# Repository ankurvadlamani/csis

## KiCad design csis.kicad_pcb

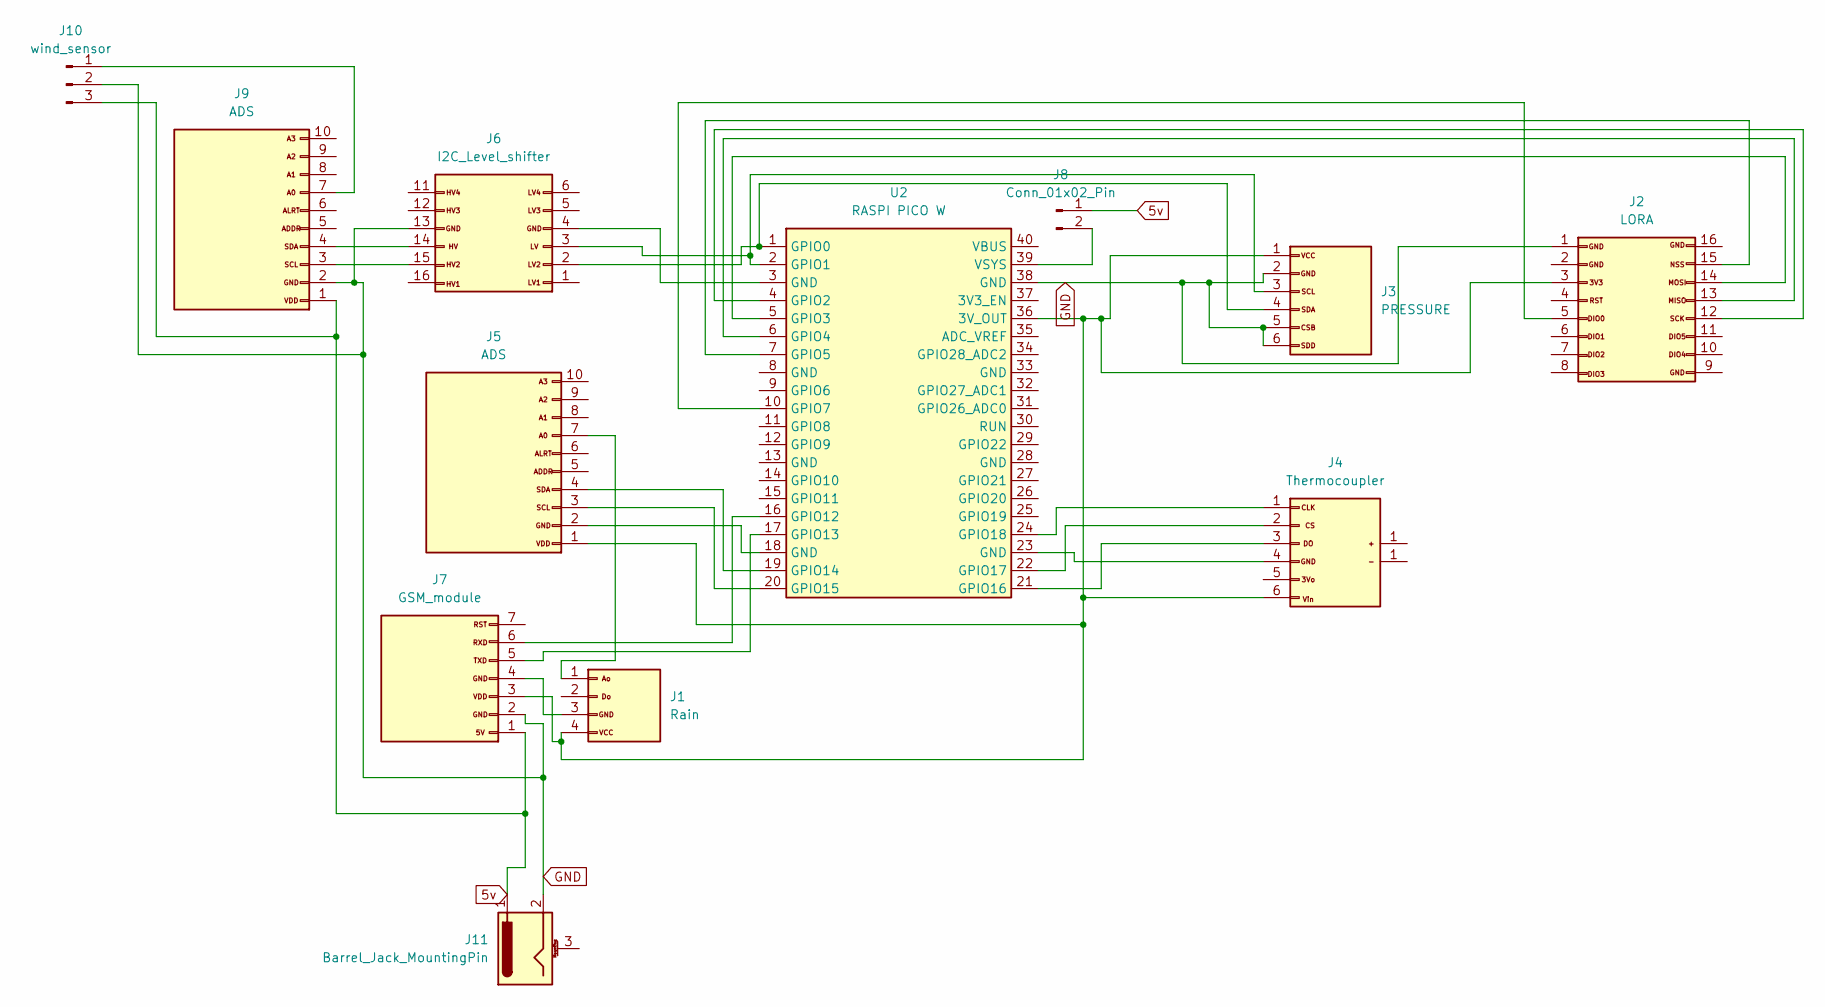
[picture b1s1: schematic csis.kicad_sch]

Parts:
J1: Rain; RAINv1
J2: LORA; lora
J3: PRESSURE; BARO
J4: Thermocoupler
J5, J9: ADS; ADS1
J6: I2C_Level_shifter; i2c_level
J7: GSM_module; GSM
J8: Conn_01x02_Pin; PinHeader_1x02_P2.54mm_Vertical
J10: wind_sensor; PinHeader_1x03_P2.54mm_Vertical
J11: Barrel_Jack_MountingPin; BarrelJack_Horizontal
U2: RASPI PICO W; PICOw

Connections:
5v: J7.1, J8.1, J9.1, J10.3, J11.1
GND: J2.1, J3.2, J3.5, J3.6 (SDD), J6.13 (Pin_5), J7.2, J9.2, J10.2, J11.2, U2.38 (GND)
unnamed: J1.1, J5.7
unnamed: J1.3, J7.4
unnamed: J1.4, J2.3, J3.1, J4.6, J5.1, J7.3, U2.36 (3V_OUT)
unnamed: J3.3, J6.3, U2.2 (GPIO1)
unnamed: J3.4, J6.2, U2.1 (GPIO0)
unnamed: J4.1, U2.24 (GPIO18)
unnamed: J4.2, U2.22 (GPIO17)
unnamed: J4.3, U2.21 (GPIO16)
unnamed: J4.4, U2.23 (GND)
unnamed: J5.2, U2.18 (GND)
unnamed: J5.3, U2.20 (GPIO15)
unnamed: J5.4, U2.19 (GPIO14)
unnamed: J6.4, U2.3 (GND)
unnamed: J7.5, U2.17 (GPIO13)
unnamed: J8.2, U2.39 (VSYS)
unnamed: J6.15 (SDD), J9.3
unnamed: J6.14 (SDD), J9.4
unnamed: J9.7, J10.1
unnamed: J2.12 (Pin_4), U2.4 (GPIO2)
unnamed: J2.14 (SDD), U2.5 (GPIO3)
unnamed: J2.13 (Pin_5), U2.6 (GPIO4)
unnamed: J2.15 (SDD), U2.7 (GPIO5)
unnamed: J2.5, U2.10 (GPIO7)
unnamed: J7.6 (SDD), U2.16 (GPIO12)

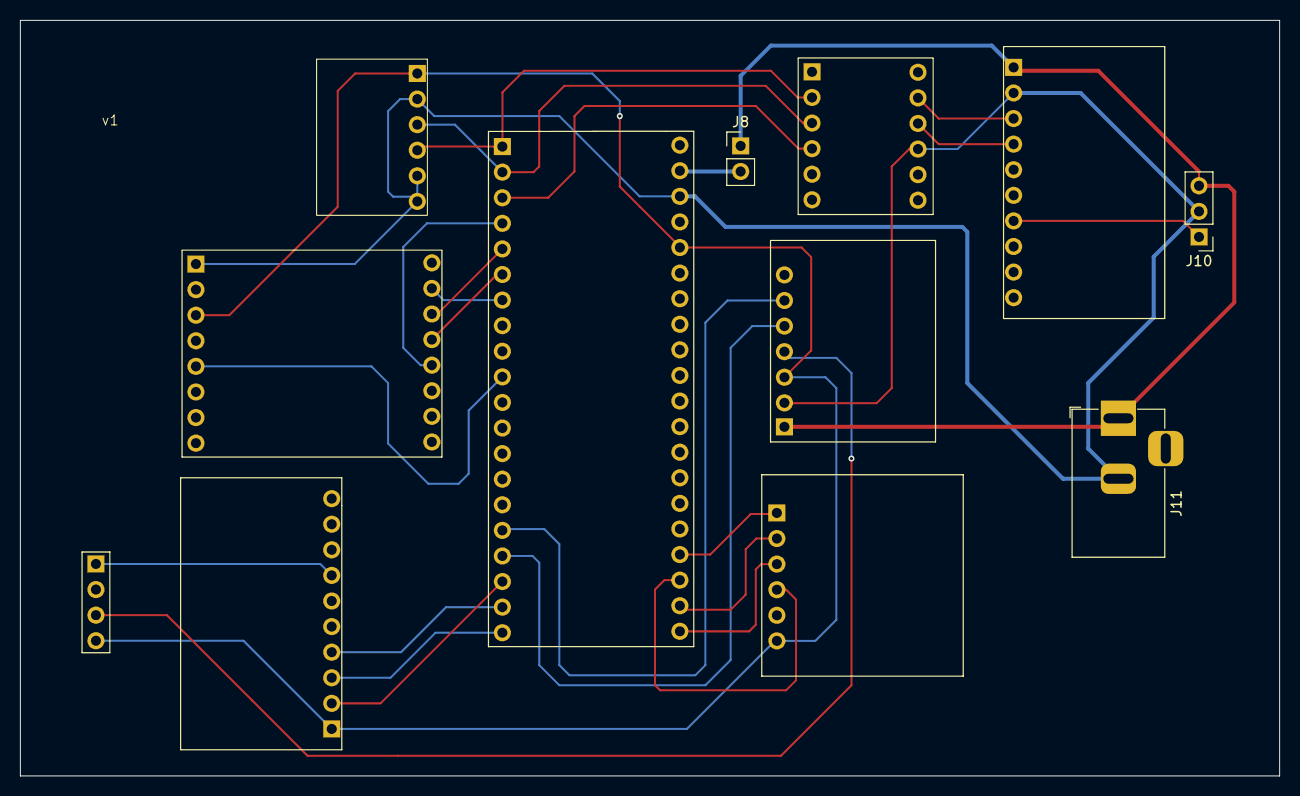
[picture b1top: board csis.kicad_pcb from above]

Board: 2 copper layers, 125.0 x 75.0 mm, 12 parts (0 on the bottom side), 26 nets.

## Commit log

2025-12-25 lora.py
2025-12-25 GSM.py
    Initialize GSM communication and send AT commands for setup.
